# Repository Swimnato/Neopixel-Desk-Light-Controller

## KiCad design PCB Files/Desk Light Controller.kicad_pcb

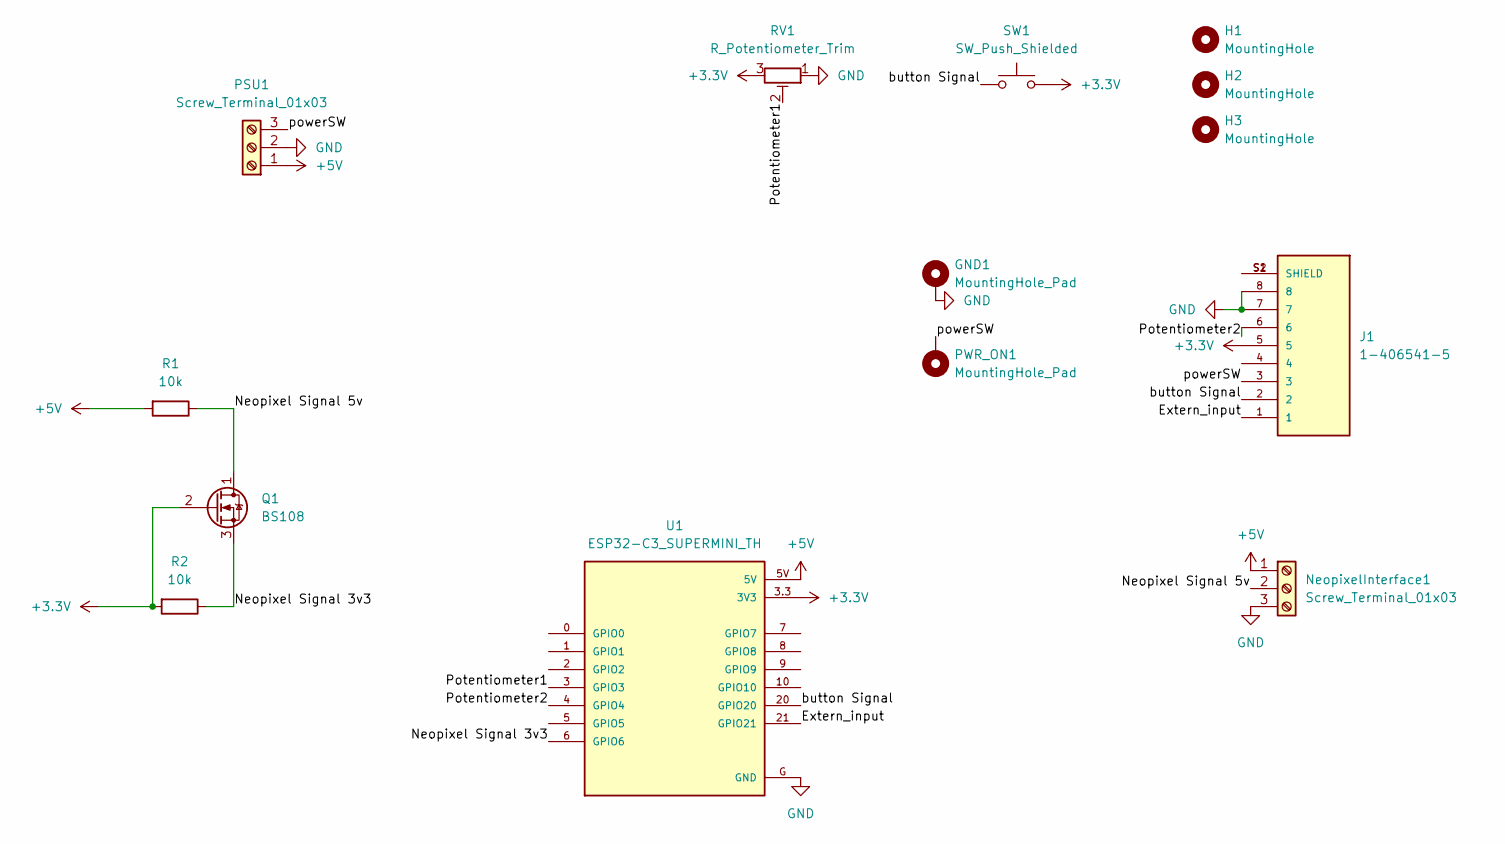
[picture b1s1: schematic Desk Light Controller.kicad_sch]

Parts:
GND1: MountingHole_Pad; Pin_D1.4mm_L8.5mm_W2.8mm_FlatFork
H1, H2, H3: MountingHole; MountingHole_3.2mm_M3
J1: 1-406541-5; TE_1-406541-5; PARTREV R
NeopixelInterface1: Screw_Terminal_01x03; TerminalBlock_MaiXu_MX126-5.0-03P_1x03_P5.00mm
PSU1: Screw_Terminal_01x03; TerminalBlock_MaiXu_MX126-5.0-03P_1x03_P5.00mm
PWR_ON1: MountingHole_Pad; Pin_D1.4mm_L8.5mm_W2.8mm_FlatFork
Q1: BS108; TO-92_Inline
R1, R2: 10k; R_Axial_DIN0204_L3.6mm_D1.6mm_P7.62mm_Horizontal
RV1: R_Potentiometer_Trim; vertical pot
SW1: SW_Push_Shielded; SW_Tactile_SPST_Angled_PTS645Vx31-2LFS
U1: ESP32-C3_SUPERMINI_TH; MODULE_ESP32-C3_SUPERMINI

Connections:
+3.3V: J1.5, Q1.2 (G), R2.2, RV1.3, SW1.2, U1.3.3 (3V3)
+5V: NeopixelInterface1.1, PSU1.1, R1.2, U1.5V
/Extern_input: J1.1, U1.21 (GPIO21)
/Neopixel Signal 3v3: Q1.3 (S), R2.1, U1.6 (GPIO6)
/Neopixel Signal 5v: NeopixelInterface1.2, Q1.1 (D), R1.1
/Potentiometer1: RV1.2, U1.3 (GPIO3)
/Potentiometer2: J1.6, U1.4 (GPIO4)
/button Signal: J1.2, SW1.1, U1.20 (GPIO20)
/powerSW: J1.3, PSU1.3, PWR_ON1.1
GND: GND1.1, J1.7, J1.8, NeopixelInterface1.3, PSU1.2, RV1.1, U1.G (GND)
unnamed: J1.S1 (SHIELD), J1.S2 (SHIELD)

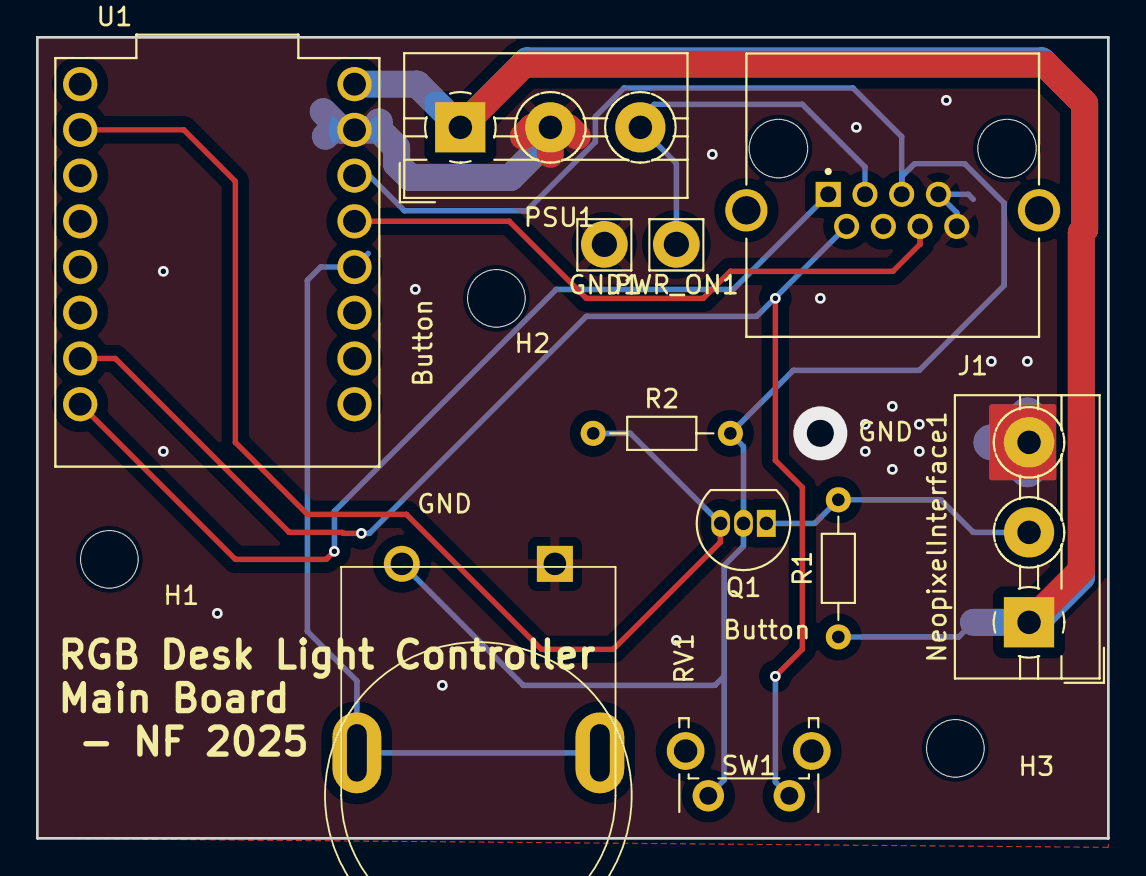
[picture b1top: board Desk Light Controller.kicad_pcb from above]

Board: 2 copper layers, 59.5 x 44.5 mm, 14 parts (0 on the bottom side), 11 nets.

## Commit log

2025-09-16 Initial Version
    Version 1.3, up until now I have kept this project private on my computer, but I have decided to make this open source. Hopefully someone finds this useful. This light controller has several modes an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
